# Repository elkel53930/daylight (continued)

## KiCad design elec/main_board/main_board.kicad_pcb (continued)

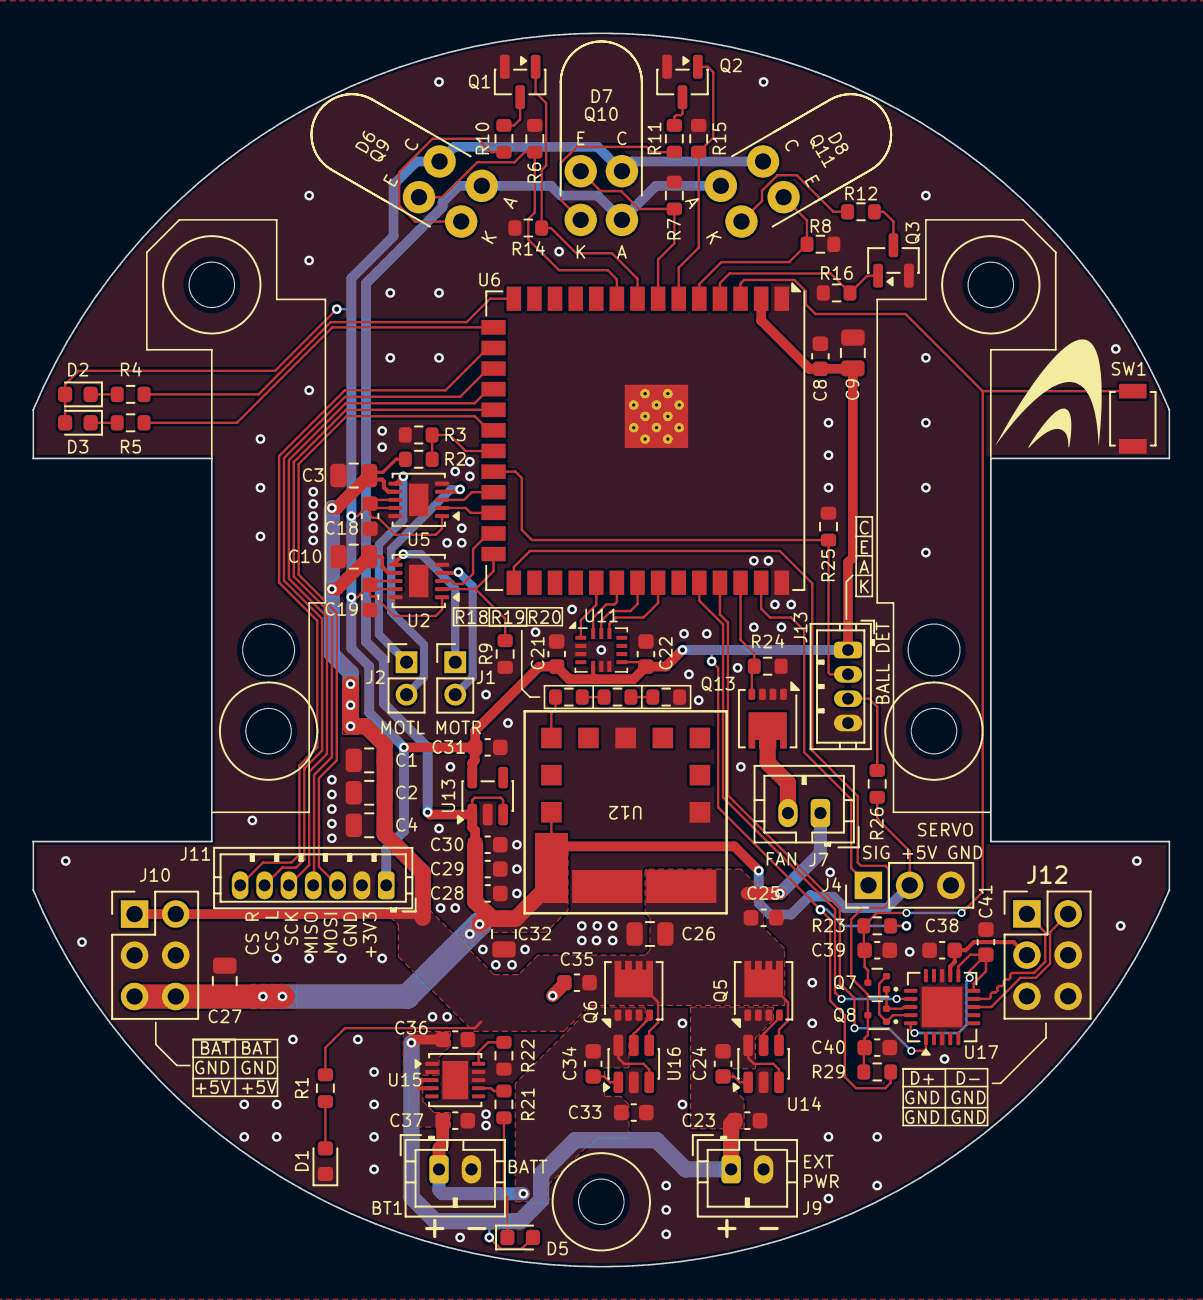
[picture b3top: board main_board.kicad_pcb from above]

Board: 2 copper layers, 70.0 x 76.0 mm, 101 parts (0 on the bottom side), 66 nets.

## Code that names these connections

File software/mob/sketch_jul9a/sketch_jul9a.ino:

#include "driver/mcpwm_prelude.h"
#include <SPI.h>

// ---- LED ----
#define LED_PIN_R   3
#define LED_PIN_G   20

// ---- Motor driver ----
#define PWM_L_PIN   21
#define CWCCW_L_PIN 47
#define PWM_R_PIN   48
#define CWCCW_R_PIN 45

// ---- Light sensor ----
#define LIGHT_L_EN_PIN  15
#define LIGHT_L_ADC_PIN 16
#define LIGHT_F_EN_PIN   6
#define LIGHT_F_ADC_PIN  7
#define LIGHT_R_EN_PIN   4
#define LIGHT_R_ADC_PIN  5

static int read_light_sensor(int en_pin, int adc_pin) {
    // 1. センサOFF状態でオフセット取得
    int offset = analogRead(adc_pin);
    // 2. センサON
    digitalWrite(en_pin, HIGH);
    // 3. 100us待つ
    delayMicroseconds(100);
    // 4. センサON状態で電圧取得
    int val = analogRead(adc_pin);
    // 5. センサOFF
    digitalWrite(en_pin, LOW);
    // 差分を返す
    return val - offset;
}

// ---- IMU (LSM6DSR) SPI ----
#define IMU_MISO 38
#define IMU_MOSI 39
#define IMU_SCK  40
#define IMU_CS   41

SPIClass imu_spi(HSPI);

static void imu_transfer(uint8_t* rx, const uint8_t* tx, size_t len) {
    imu_spi.beginTransaction(SPISettings(500000, MSBFIRST, SPI_MODE3));
    digitalWrite(IMU_CS, LOW);
    delayMicroseconds(50);
    for (size_t i = 0; i < len; i++) rx[i] = imu_spi.transfer(tx[i]);
    delayMicroseconds(50);
    digitalWrite(IMU_CS, HIGH);
    imu_spi.endTransaction();
}

static void imu_write_reg(uint8_t reg, uint8_t val) {
    uint8_t tx[2] = {reg, val};
    uint8_t rx[2];
    imu_transfer(rx, tx, 2);
}

static uint8_t imu_read_reg(uint8_t reg) {
    uint8_t tx[2] = {(uint8_t)(reg | 0x80), 0xFF};
    uint8_t rx[2] = {0, 0};
    imu_transfer(rx, tx, 2);
    return rx[1];
}

static int16_t imu_read_gyro_z() {
    // OUTZ_L_G=0x26, OUTZ_H_G=0x27 を連続読み出し (auto-increment)
    uint8_t tx[3] = {0x26 | 0x80, 0xFF, 0xFF};
    uint8_t rx[3] = {0, 0, 0};
    imu_transfer(rx, tx, 3);
    return (int16_t)((rx[2] << 8) | rx[1]);
}

static bool imu_init() {
    // ソフトウェアリセット
    imu_write_reg(0x12, 0x01);
    delay(50);
    // CTRL3_C: BDU + IF_INC
    imu_write_reg(0x12, 0x44);
    // CTRL2_G: ODR=416Hz, FS=±1000dps
    imu_write_reg(0x11, 0x68);
    // CTRL1_XL: ODR=416Hz, FS=±4g
    imu_write_reg(0x10, 0x68);
    delay(100);
    uint8_t who = imu_read_reg(0x0F);
    Serial.printf("[IMU] WHO_AM_I = 0x%02X (expect 0x6B)\n", who);
    return (who == 0x6B);
}

// MCPWM: 40kHz, 50% duty
// resolution 80MHz / period 2000ticks = 40kHz, compare 1000 = 50%
static void motor_pwm_init() {
    mcpwm_timer_handle_t timer = NULL;
    mcpwm_timer_config_t timer_cfg = {};
    timer_cfg.group_id      = 0;
    timer_cfg.clk_src       = MCPWM_TIMER_CLK_SRC_DEFAULT;
    timer_cfg.resolution_hz = 80000000;
    timer_cfg.count_mode    = MCPWM_TIMER_COUNT_MODE_UP;
    timer_cfg.period_ticks  = 2000;  // 80MHz / 2000 = 40kHz
    mcpwm_new_timer(&timer_cfg, &timer);

    mcpwm_operator_config_t oper_cfg = {};
    oper_cfg.group_id = 0;

    mcpwm_oper_handle_t oper_r = NULL, oper_l = NULL;
    mcpwm_new_operator(&oper_cfg, &oper_r);
    mcpwm_new_operator(&oper_cfg, &oper_l);
    mcpwm_operator_connect_timer(oper_r, timer);
    mcpwm_operator_connect_timer(oper_l, timer);

    mcpwm_comparator_config_t cmp_cfg = {};
    cmp_cfg.flags.update_cmp_on_tez = true;

    mcpwm_cmpr_handle_t cmpr_r = NULL, cmpr_l = NULL;
    mcpwm_new_comparator(oper_r, &cmp_cfg, &cmpr_r);
    mcpwm_new_comparator(oper_l, &cmp_cfg, &cmpr_l);
    mcpwm_comparator_set_compare_value(cmpr_r, 1000);  // 50% duty
    mcpwm_comparator_set_compare_value(cmpr_l, 1000);  // 50% duty

    mcpwm_gen_handle_t gen_r = NULL, gen_l = NULL;
    mcpwm_generator_config_t gen_cfg = {};

    gen_cfg.gen_gpio_num = PWM_R_PIN;
    mcpwm_new_generator(oper_r, &gen_cfg, &gen_r);
    gen_cfg.gen_gpio_num = PWM_L_PIN;
    mcpwm_new_generator(oper_l, &gen_cfg, &gen_l);

    // タイマー周期の先頭でHIGH、コンペアマッチでLOW → Duty=compare/period
    mcpwm_generator_set_action_on_timer_event(gen_r,
        MCPWM_GEN_TIMER_EVENT_ACTION(MCPWM_TIMER_DIRECTION_UP, MCPWM_TIMER_EVENT_EMPTY, MCPWM_GEN_ACTION_HIGH));
    mcpwm_generator_set_action_on_compare_event(gen_r,
        MCPWM_GEN_COMPARE_EVENT_ACTION(MCPWM_TIMER_DIRECTION_UP, cmpr_r, MCPWM_GEN_ACTION_LOW));

    mcpwm_generator_set_action_on_timer_event(gen_l,
        MCPWM_GEN_TIMER_EVENT_ACTION(MCPWM_TIMER_DIRECTION_UP, MCPWM_TIMER_EVENT_EMPTY, MCPWM_GEN_ACTION_HIGH));
    mcpwm_generator_set_action_on_compare_event(gen_l,
        MCPWM_GEN_COMPARE_EVENT_ACTION(MCPWM_TIMER_DIRECTION_UP, cmpr_l, MCPWM_GEN_ACTION_LOW));

    mcpwm_timer_enable(timer);
    mcpwm_timer_start_stop(timer, MCPWM_TIMER_START_NO_STOP);
}

void setup() {
    Serial.begin(115200);

    // LED
    pinMode(LED_PIN_R, OUTPUT);
    pinMode(LED_PIN_G, OUTPUT);
    digitalWrite(LED_PIN_R, HIGH);  // 消灯
    digitalWrite(LED_PIN_G, HIGH);  // 消灯

    // 光センサ (左・前・右)
    pinMode(LIGHT_L_EN_PIN, OUTPUT); digitalWrite(LIGHT_L_EN_PIN, LOW);
    pinMode(LIGHT_F_EN_PIN, OUTPUT); digitalWrite(LIGHT_F_EN_PIN, LOW);
    pinMode(LIGHT_R_EN_PIN, OUTPUT); digitalWrite(LIGHT_R_EN_PIN, LOW);
    analogReadResolution(12);  // 12bit (0-4095)

    // モータドライバ方向制御
    pinMode(CWCCW_L_PIN, OUTPUT);
    pinMode(CWCCW_R_PIN, OUTPUT);
    digitalWrite(CWCCW_L_PIN, LOW);
    digitalWrite(CWCCW_R_PIN, LOW);

    // モータドライバ PWM (MCPWM: 40kHz, 50%)
    motor_pwm_init();

    // IMU SPI初期化
    pinMode(IMU_CS, OUTPUT);
    digitalWrite(IMU_CS, HIGH);
    imu_spi.begin(IMU_SCK, IMU_MISO, IMU_MOSI, IMU_CS);
    if (!imu_init()) {
        Serial.println("[IMU] init FAILED");
    } else {
        Serial.println("[IMU] init OK");
    }
}

void loop() {
    // Phase A: LED_R点灯 / LED_G消灯、CWCCW = HIGH
    digitalWrite(LED_PIN_R, LOW);   // 点灯
    digitalWrite(LED_PIN_G, HIGH);  // 消灯
    digitalWrite(CWCCW_L_PIN, HIGH);
    digitalWrite(CWCCW_R_PIN, HIGH);
    {
        int16_t raw = imu_read_gyro_z();
        float dps = raw * 0.035f;
        uint32_t t0 = micros();
        int lL = read_light_sensor(LIGHT_L_EN_PIN, LIGHT_L_ADC_PIN);
        int lF = read_light_sensor(LIGHT_F_EN_PIN, LIGHT_F_ADC_PIN);
        int lR = read_light_sensor(LIGHT_R_EN_PIN, LIGHT_R_ADC_PIN);
        uint32_t elapsed = micros() - t0;
        Serial.printf("[Gyro Z] raw=%6d  %.2f deg/s  [Light L/F/R] %4d %4d %4d  (%u us)\n", raw, dps, lL, lF, lR, elapsed);
    }
    delay(500);

    // Phase B: LED_R消灯 / LED_G点灯、CWCCW = LOW
    digitalWrite(LED_PIN_R, HIGH);  // 消灯
    digitalWrite(LED_PIN_G, LOW);   // 点灯
    digitalWrite(CWCCW_L_PIN, LOW);
    digitalWrite(CWCCW_R_PIN, LOW);
    {
        int16_t raw = imu_read_gyro_z();
        float dps = raw * 0.035f;
        uint32_t t0 = micros();
        int lL = read_light_sensor(LIGHT_L_EN_PIN, LIGHT_L_ADC_PIN);
        int lF = read_light_sensor(LIGHT_F_EN_PIN, LIGHT_F_ADC_PIN);
        int lR = read_light_sensor(LIGHT_R_EN_PIN, LIGHT_R_ADC_PIN);
        uint32_t elapsed = micros() - t0;
        Serial.printf("[Gyro Z] raw=%6d  %.2f deg/s  [Light L/F/R] %4d %4d %4d  (%u us)\n", raw, dps, lL, lF, lR, elapsed);
    }
    delay(500);
}

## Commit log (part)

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2026-05-14 Initial design of main board.
2026-05-14 Remove unused file
2026-06-06 アートワーク完了
2026-06-27 再設計 部品配置完了
2026-06-28 配線作業中
2026-06-29 アートワーク完了、発注
